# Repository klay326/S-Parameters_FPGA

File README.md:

# S-Parameters_FPGA
FPGA S Parameter Measuring Tool Suite to Aid TTU Instructor Derek Johnston with Fraudulent IC Indentification

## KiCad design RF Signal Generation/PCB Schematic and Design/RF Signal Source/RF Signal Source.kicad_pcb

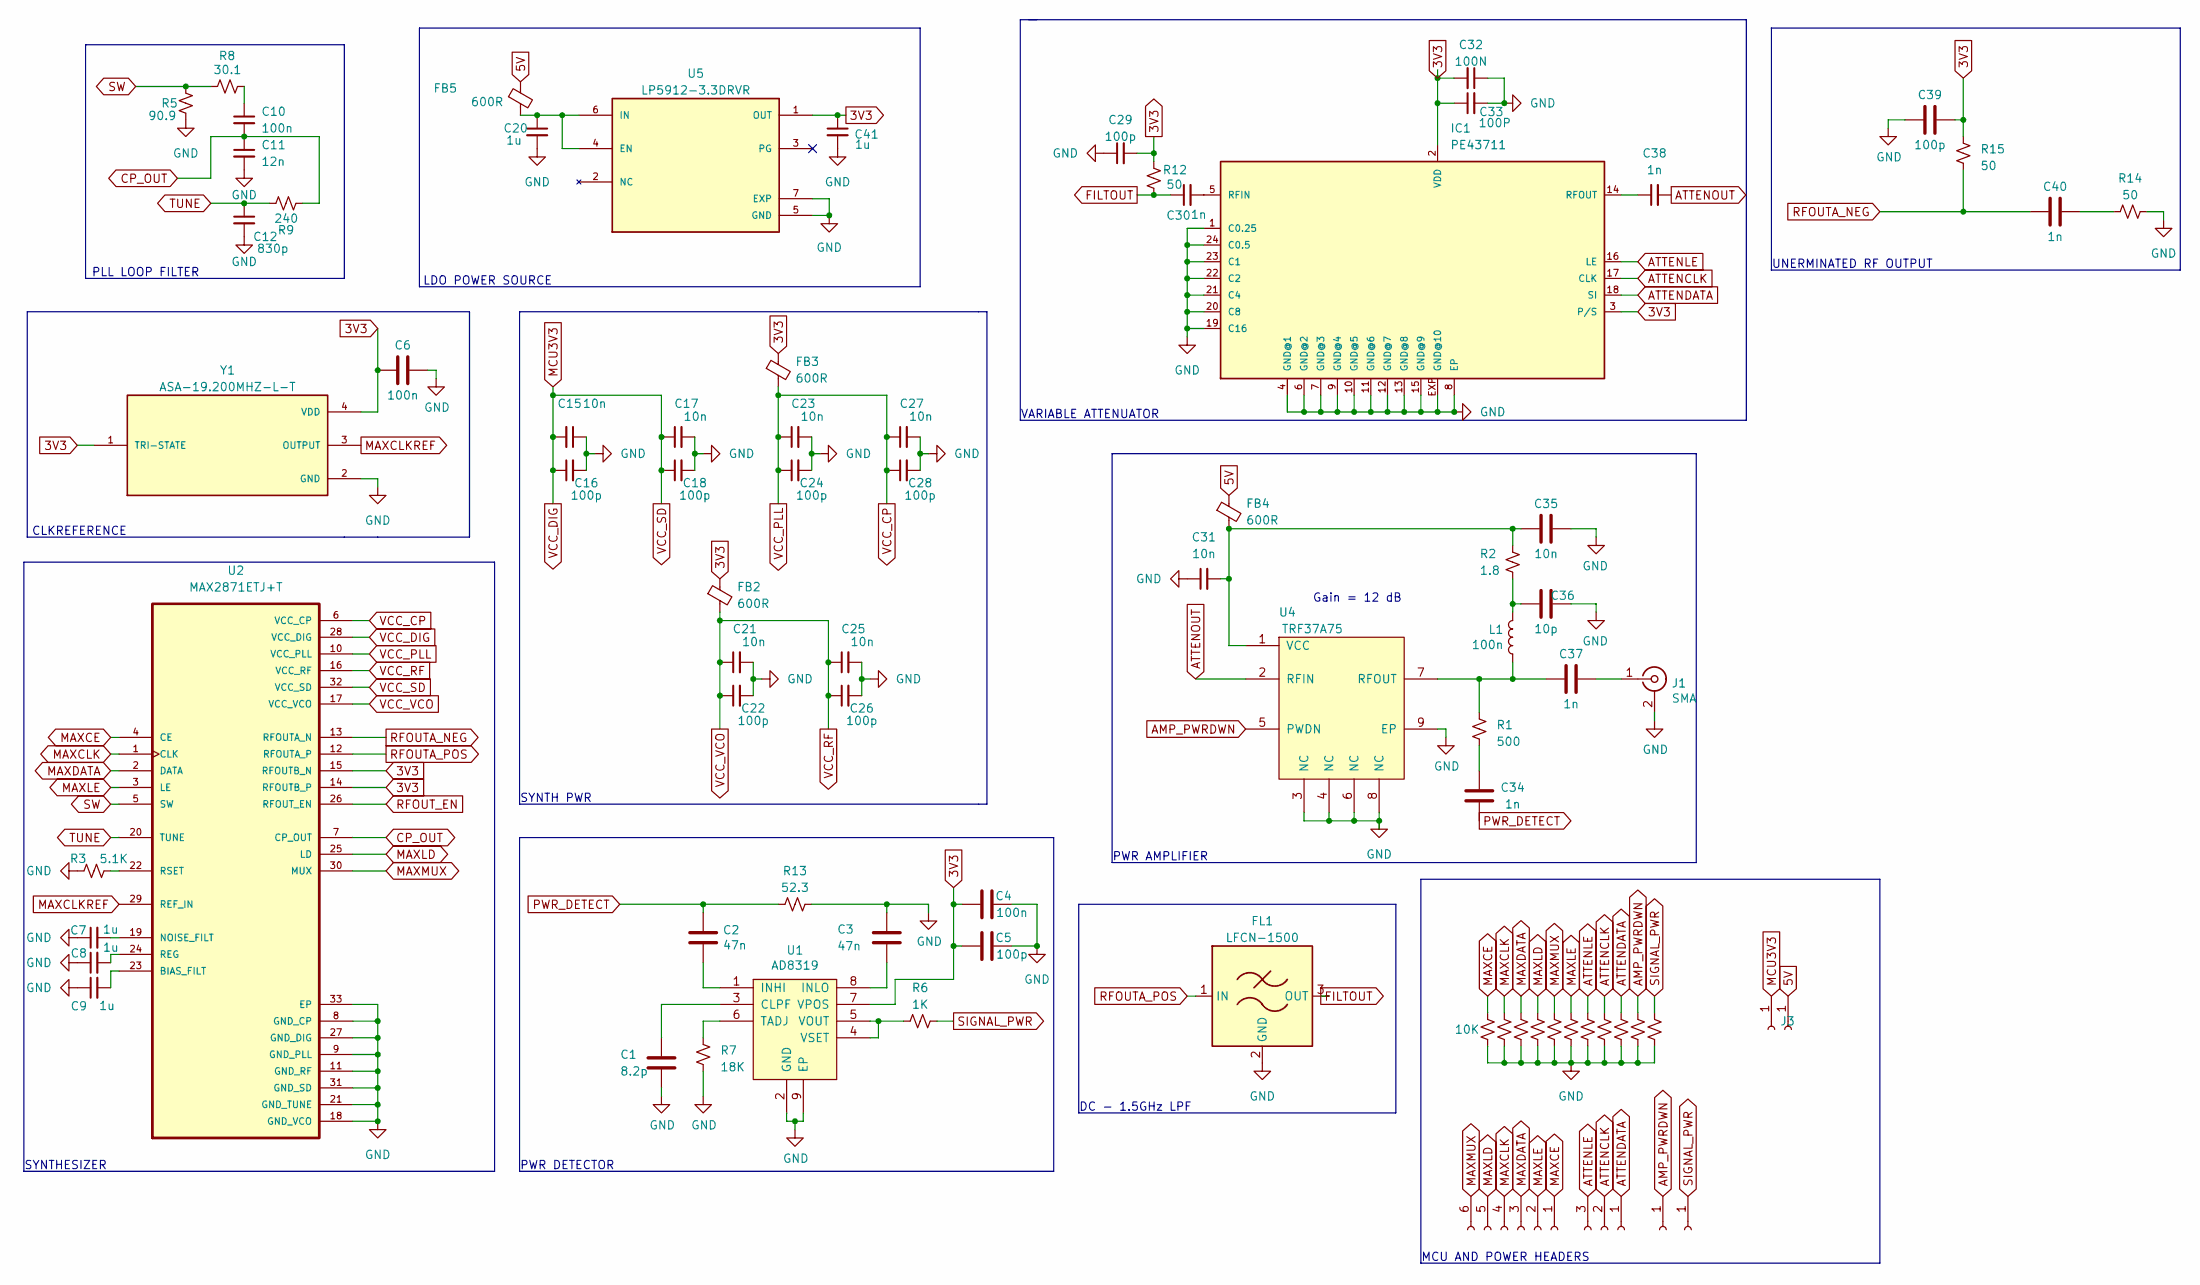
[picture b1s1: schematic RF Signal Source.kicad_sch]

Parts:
C1: 8.2p; C_0402_1005Metric
C2, C3: 47n; C_0402_1005Metric
C4, C6, C10: 100n; C_0402_1005Metric
C5, C16, C18, C22, C24, C26, C28, C29, C39: 100p; C_0402_1005Metric
C7, C8, C9, C20, C41: 1u; C_0402_1005Metric
C11: 12n; C_0402_1005Metric
C12: 830p; C_0402_1005Metric
C15, C17, C21, C23, C25, C27, C31, C35: 10n; C_0402_1005Metric
C30, C34, C37, C38, C40: 1n; C_0402_1005Metric
C32: 100N; C_0402_1005Metric
C33: 100P; C_0402_1005Metric
C36: 10p; C_0402_1005Metric
FB2, FB3, FB4, FB5: 600R; BEADC0603X33N
FL1: LFCN-1500; Filter_Mini-Circuits_FV1206
IC1: PE43711; VQFN24-4X4
J1: SMA; LINX_CONSMA002-G
J3, J7, J8: Conn_01x01_Socket; PinHeader_1x01_P2.54mm_Vertical
J4: Conn_01x01_Socket; PinSocket_1x01_P2.54mm_Vertical
J5: Conn_01x06_Socket; PinHeader_1x06_P2.54mm_Vertical
J6: Conn_01x03_Socket; PinHeader_1x03_P2.54mm_Vertical
L1: 100n; L_0402_1005Metric
R1: 500; R_0402_1005Metric
R2: 1.8; R_0402_1005Metric
R3: 5.1K; R_0402_1005Metric
R4, R10, R11, R16, R17, R18, R19, R20, R21, R22, R23: 10K; R_0402_1005Metric
R5: 90.9; R_0402_1005Metric
R6: 1K; R_0402_1005Metric
R7: 18K; R_0402_1005Metric
R8: 30.1; R_0402_1005Metric
R9: 240; R_0402_1005Metric
R12, R14, R15: 50; R_0402_1005Metric
R13: 52.3; R_0402_1005Metric
U1: AD8319; DFN-8-1EP_2x3mm_P0.5mm_EP0.61x2.2mm; DigiKey AD8319ACPZ-R7CT-ND
U2: MAX2871ETJ+T; QFN-32-1EP_5x5mm_P0.5mm_EP3.3x3.3mm_ThermalVias
U4: TRF37A75; DFN-8-1EP_2x2mm_P0.5mm_EP0.9x1.5mm; DigiKey 296-37886-1-ND
U5: LP5912-3.3DRVR; SON65P200X200X80-7N; PARTREV D
Y1: ASA-19.200MHZ-L-T; XTAL_ASA-19.200MHZ-L-T; PARTREV 01.24.14

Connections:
3V3: C4.2, C5.2, C6.2, C29.2, C32.2, C33.1, C39.1, C41.1, FB2.1, FB3.1, IC1.2 (VDD), IC1.3 (P/S), R12.1, R15.1, U1.7 (VPOS), U2.14 (RFOUTB_P), U2.15 (RFOUTB_N), U5.1 (OUT), Y1.1 (TRI-STATE), Y1.4 (VDD)
5V: FB4.1, FB5.1, J4.1
AMP_PWRDWN: J7.1, R22.1, U4.5 (PWDN)
ATTENCLK: IC1.17 (CLK), J6.2, R20.1
ATTENDATA: IC1.18 (SI), J6.1, R21.1
ATTENLE: IC1.16 (LE), J6.3, R19.1
ATTENOUT: C38.2, U4.2 (RFIN)
CP_OUT: C10.2, C11.1, R9.2, U2.7 (CP_OUT)
FILTOUT: C30.1, FL1.3 (OUT), R12.2
GND: C1.2, C3.1, C4.1, C5.1, C6.1, C7.1, C8.1, C9.1, C11.2, C12.2, C15.1, C16.2, C17.2, C18.2, C20.2, C21.2, C22.2, C23.2, C24.2, C25.2, C26.2, C27.2, C28.2, C29.1, C31.1, C32.1, C33.2, C35.2, C36.2, C39.2, C41.2, FL1.2 (GND), FL1.4 (GND), IC1.1 (C0.25), IC1.4 (GND@1), IC1.6 (GND@2), IC1.7 (GND@3), IC1.8 (EP), IC1.9 (GND@4), IC1.10 (GND@5), IC1.11 (GND@6), IC1.12 (GND@7), IC1.13 (GND@8), IC1.15 (GND@9), IC1.19 (C16), IC1.20 (C8), IC1.21 (C4), IC1.22 (C2), IC1.23 (C1), IC1.24 (C0.5), IC1.EXP (GND@10), J1.2 (Ext), J1.S1, J1.S2, J1.S3, J1.S4, R3.1, R4.2, R5.2, R7.2, R10.2, R11.2, R13.2, R14.2, R16.2, R17.2, R18.2, R19.2, R20.2, R21.2, R22.2, R23.2, U1.2 (GND), U1.9 (EP), U2.8 (GND_CP), U2.9 (GND_PLL), U2.11 (GND_RF), U2.18 (GND_VCO), U2.21 (GND_TUNE), U2.27 (GND_DIG), U2.31 (GND_SD), U2.33 (EP), U4.3 (NC), U4.4 (NC), U4.6 (NC), U4.8 (NC), U4.9 (EP), U5.5 (GND), U5.7 (EXP), Y1.2 (GND)
MAXCE: J5.1, R4.1, U2.4 (CE)
MAXCLK: J5.4, R10.1, U2.1 (CLK)
MAXCLKREF: U2.29 (REF_IN), Y1.3 (OUTPUT)
MAXDATA: J5.3, R11.1, U2.2 (DATA)
MAXLD: J5.5, R16.1, U2.25 (LD)
MAXLE: J5.2, R18.1, U2.3 (LE)
MAXMUX: J5.6, R17.1, U2.30 (MUX)
MCU3V3: C15.2, C16.1, C17.1, C18.1, J3.1, U2.28 (VCC_DIG), U2.32 (VCC_SD)
unnamed: C10.1, R8.2
unnamed: C34.1, R1.2
unnamed: C36.1, L1.1, R2.2
unnamed: C40.1, R14.1
unnamed: C30.2, IC1.5 (RFIN)
unnamed: C38.1, IC1.14 (RFOUT)
unnamed: C37.1, J1.1 (In)
unnamed: C1.1, U1.3 (CLPF)
unnamed: C2.2, U1.1 (INHI)
unnamed: C3.2, U1.8 (INLO)
unnamed: R7.1, U1.6 (TADJ)
unnamed: R6.1, U1.4 (VSET), U1.5 (VOUT)
unnamed: C9.2, U2.23 (BIAS_FILT)
unnamed: C7.2, U2.19 (NOISE_FILT)
unnamed: C8.2, U2.24 (REG)
unnamed: R3.2, U2.22 (RSET)
unnamed: C37.2, L1.2, R1.1, U4.7 (RFOUT)
unnamed: C31.2, C35.1, FB4.2, R2.1, U4.1 (VCC)
unnamed: C20.1, FB5.2, U5.4 (EN), U5.6 (IN)
PWR_DETECT: C2.1, C34.2, R13.1
RFOUTA_NEG: C40.2, R15.2, U2.13 (RFOUTA_N)
RFOUTA_POS: FL1.1 (IN), U2.12 (RFOUTA_P)
RFOUT_EN: U2.26 (RFOUT_EN)
SIGNAL_PWR: J8.1, R6.2, R23.1
SW: R5.1, R8.1, U2.5 (SW)
TUNE: C12.1, R9.1, U2.20 (TUNE)
VCC_CP: C23.1, C24.1, C27.1, C28.1, FB3.2, U2.6 (VCC_CP), U2.10 (VCC_PLL)
VCC_RF: C21.1, C22.1, C25.1, C26.1, FB2.2, U2.16 (VCC_RF), U2.17 (VCC_VCO)

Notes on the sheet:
DC - 1.5GHz LPF
MCU AND POWER HEADERS
LDO POWER SOURCE
UNERMINATED RF OUTPUT
SYNTH PWR
VARIABLE ATTENUATOR
Gain = 12 dB
PWR DETECTOR
PWR AMPLIFIER
CLKREFERENCE
PLL LOOP FILTER
SYNTHESIZER

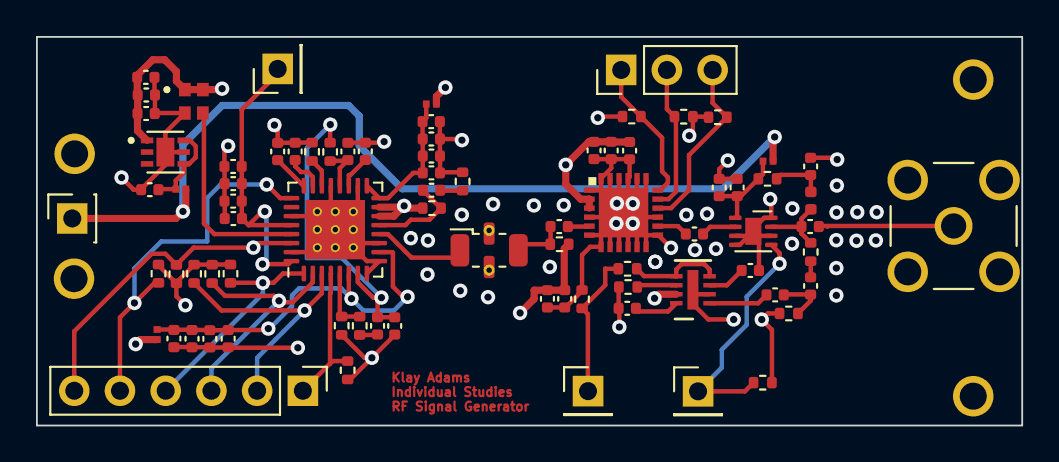
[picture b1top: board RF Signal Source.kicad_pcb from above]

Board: 4 copper layers, 54.7 x 21.6 mm, 80 parts (0 on the bottom side), 45 nets.

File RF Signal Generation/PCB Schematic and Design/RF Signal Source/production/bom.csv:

Designator,Footprint,Quantity,Value,LCSC Part #
"_4, _3, _2, ",,4,,
C1,0402,1,8.2p,
C10,0402,1,100n,
C11,0402,1,12n,
C12,0402,1,830p,
C15,0402,1,10n,
C16,0402,1,100p,
C17,0402,1,10n,
C18,0402,1,100p,
C2,0402,1,47n,
C20,0402,1,1u,
C21,0402,1,10n,
C22,0402,1,100p,
C23,0402,1,10n,
C24,0402,1,100p,
C25,0402,1,10n,
C26,0402,1,100p,
C27,0402,1,10n,
C28,0402,1,100p,
C29,0402,1,100p,
C3,0402,1,47n,
C30,0402,1,1n,
C31,0402,1,10n,
C32,0402,1,100N,
C33,0402,1,100P,
C34,0402,1,1n,
C35,0402,1,10n,
C36,0402,1,10p,
C37,0402,1,1n,
C38,0402,1,1n,
C39,0402,1,100p,
C4,0402,1,100n,
C40,0402,1,1n,
C41,0402,1,1u,
C5,0402,1,100p,
C6,0402,1,100n,
C7,0402,1,1u,
C8,0402,1,1u,
C9,0402,1,1u,
"FB2, FB3, FB4, FB5",BEADC0603X33N,4,600R,
FL1,Filter_Mini-Circuits_FV1206,1,LFCN-1500,
IC1,VQFN24-4X4,1,PE43711,
J1,LINX_CONSMA002-G,1,SMA,
"J3, J7, J8",PinHeader_1x01_P2.54mm_Vertical,3,Conn_01x01_Socket,
J4,PinSocket_1x01_P2.54mm_Vertical,1,Conn_01x01_Socket,
J5,PinHeader_1x06_P2.54mm_Vertical,1,Conn_01x06_Socket,
J6,PinHeader_1x03_P2.54mm_Vertical,1,Conn_01x03_Socket,
L1,0402,1,100n,
R1,0402,1,500R,
R10,0402,1,10K,
R11,0402,1,10K,
R12,0402,1,50,
R13,0402,1,52.3,
R14,0402,1,50,
R15,0402,1,50,
R16,0402,1,10K,
R17,0402,1,10K,
R18,0402,1,10K,
R19,0402,1,10K,
R2,0402,1,1R8,
R20,0402,1,10K,
R21,0402,1,10K,
R22,0402,1,10K,
R23,0402,1,10K,
R3,0402,1,5.1K,
R4,0402,1,10K,
R5,0402,1,90.9,
R6,0402,1,1K,
R7,0402,1,18K,
R8,0402,1,30.1,
R9,0402,1,240,
U1,DFN-8-1EP_2x3mm_P0.5mm_EP0.61x2.2mm,1,AD8319,
U2,QFN-32-1EP_5x5mm_P0.5mm_EP3.3x3.3mm_ThermalVias,1,MAX2871ETJ+T,
U4,DFN-8-1EP_2x2mm_P0.5mm_EP0.9x1.5mm,1,TRF37A75,
U5,SON65P200X200X80-7N,1,LP5912-3.3DRVR,
Y1,XTAL_ASA-19.200MHZ-L-T,1,ASA-19.200MHZ-L-T,

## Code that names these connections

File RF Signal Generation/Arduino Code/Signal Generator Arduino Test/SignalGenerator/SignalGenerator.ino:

#include <SPI.h>

// Define the pins used for communication with the MAX2871
#define MAXMUX_PIN 2
#define MAXLD_PIN 3
#define MAXCLK_PIN 4
#define MAXDATA_PIN 5
#define MAXLE_PIN 6
#define MAXCE_PIN 7

// Define the pins used for communication with the AD8319
#define AD8319_DATA_PIN A0

// Define the pins used for communication with the PE43711
#define PE43711_LE_PIN 8
#define PE43711_DATA_PIN 9
#define PE43711_CLK_PIN 10

// Define the pins used for communication with the TRF75
#define TRF75_ENABLE_PIN 11

// Define the SPI settings
#define SPI_CLOCK 4000000
#define SPI_MODE SPI_MODE3
#define SPI_BIT_ORDER MSBFIRST

// Define the default values for the components
#define DEFAULT_FREQUENCY 5000000000
#define DEFAULT_OUTPUT_POWER 0
#define DEFAULT_ATTENUATION 0

// Define the variables for the components
unsigned long frequency = DEFAULT_FREQUENCY;
int output_power = DEFAULT_OUTPUT_POWER;
int attenuation = DEFAULT_ATTENUATION;

void setup() {
  // Initialize the SPI bus
  SPI.begin();
  SPI.setClockDivider(SPI_CLOCK);
  SPI.setDataMode(SPI_MODE);
  SPI.setBitOrder(SPI_BIT_ORDER);

  // Initialize the pins for the MAX2871
  pinMode(MAXMUX_PIN, OUTPUT);
  digitalWrite(MAXMUX_PIN, LOW);
  pinMode(MAXLD_PIN, OUTPUT);
  digitalWrite(MAXLD_PIN, HIGH);
  pinMode(MAXCLK_PIN, OUTPUT);
  pinMode(MAXDATA_PIN, OUTPUT);
  pinMode(MAXLE_PIN, OUTPUT);
  digitalWrite(MAXLE_PIN, HIGH);
  pinMode(MAXCE_PIN, OUTPUT);
  digitalWrite(MAXCE_PIN, HIGH);

  // Initialize the pins for the AD8319
  pinMode(AD8319_DATA_PIN, INPUT);

  // Initialize the pins for the PE43711
  pinMode(PE43711_LE_PIN, OUTPUT);
  digitalWrite(PE43711_LE_PIN, HIGH);
  pinMode(PE43711_DATA_PIN, OUTPUT);
  pinMode(PE43711_CLK_PIN, OUTPUT);
  digitalWrite(PE43711_CLK_PIN, LOW);

  // Initialize the pins for the TRF75
  pinMode(TRF75_ENABLE_PIN, OUTPUT);
  digitalWrite(TRF75_ENABLE_PIN, LOW);

  // Initialize the components
  max2871_init();
  ad8319_init();
  pe43711_init();
  trf75_init();
}

void loop() {
  // Change the frequency of the MAX2871
  frequency = 200000000;
  max2871_set_frequency(frequency);

  // Change the output power of the MAX2871 and TRF75
  output_power = -10;
  max2871_set_output_power(output_power);
  trf75_set_output_power(output_power);

  // Change the attenuation of the PE43711
  attenuation = 4;
  pe43711_set_attenuation(attenuation);

  // Change the output power of the AD8319
  output_power = -20;
  ad8319_set_output_power(output_power);

  delay(1000);
}

// Functions for the MAX2871
void max2871_init() {
  // Set the default values
  max2871_set_frequency(DEFAULT_FREQUENCY);
  max2871_set_output_power(DEFAULT_OUTPUT_POWER);
}

void max2871_set_frequency(unsigned long freq) {
  // Calculate the frequency control word
  unsigned long fword = freq * pow(2, 24) / 1000000000;

  // Send the frequency control word over SPI
  for (int i = 0; i < 24; i++) {
    digitalWrite(MAXDATA_PIN, (fword >> (23 - i)) & 0x01);
    digitalWrite(MAXCLK_PIN, HIGH);
    digitalWrite(MAXCLK_PIN, LOW);
  }

  // Latch the frequency control word
  digitalWrite(MAXLE_PIN, LOW);
  digitalWrite(MAXLE_PIN, HIGH);
}

void max2871_set_output_power(int power) {
  // Calculate the output power control word
  int pword = (power + 18) / 6;

  // Send the output power control word over SPI
  for (int i = 0; i < 6; i++) {
  digitalWrite(MAXDATA_PIN, (pword >> (5 - i)) & 0x01);
  digitalWrite(MAXCLK_PIN, HIGH);
  digitalWrite(MAXCLK_PIN, LOW);
}
  // Latch the output power control word
  digitalWrite(MAXLE_PIN, LOW);
  digitalWrite(MAXLE_PIN, HIGH);
}

// Functions for the AD8319
void ad8319_init() {
  // Set the default values
  ad8319_set_output_power(DEFAULT_OUTPUT_POWER);
}

void ad8319_set_output_power(int power) {
// Calculate the output power voltage
  float voltage = pow(10, power / 20.0);
}

// Functions for the PE43711
void pe43711_init() {
// Set the default values
pe43711_set_attenuation(DEFAULT_ATTENUATION);
}
  void pe43711_set_attenuation(int attenuation) {
  // Calculate the attenuation control word
  int aword = (attenuation + 31) * 2;

  // Send the attenuation control word over SPI
  digitalWrite(PE43711_LE_PIN, LOW);
  digitalWrite(PE43711_CLK_PIN, LOW);
  for (int i = 0; i < 7; i++) {
    digitalWrite(PE43711_DATA_PIN, (aword >> (6 - i)) & 0x01);
    digitalWrite(PE43711_CLK_PIN, HIGH);
    digitalWrite(PE43711_CLK_PIN, LOW);
  }
  digitalWrite(PE43711_LE_PIN, HIGH);
}

// Functions for the TRF75
void trf75_init() {
  // Set the default values
  trf75_set_output_power(DEFAULT_OUTPUT_POWER);
}

void trf75_set_output_power(int power) {
  // Calculate the output power voltage
  float voltage = pow(10, power / 20.0) * 0.2;

  // Send the voltage to the enable pin
  if (voltage > -1) {
    digitalWrite(TRF75_ENABLE_PIN, HIGH);
  } else {
    digitalWrite(TRF75_ENABLE_PIN, LOW);
  }
}

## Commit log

2023-01-19 Create How to Take a S-Parameter Measurement
2023-05-01 Added Pictures
2023-05-01 Pictures Cont
2023-05-08 Added project writeup
